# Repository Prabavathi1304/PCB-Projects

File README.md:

# PCB Design Projects

## Skills
- KiCad 10.0
- 2-Layer & 4-Layer PCB Design
- Schematic Design
- Gerber Export

## Projects
1. LED Circuit PCB
2. Power Supply PCB (L7805)
3. Arduino Shield PCB
4. MCU Board - ATtiny85 (4-Layer)

## Tools
- KiCad 10.0
- ERC & DRC Verification

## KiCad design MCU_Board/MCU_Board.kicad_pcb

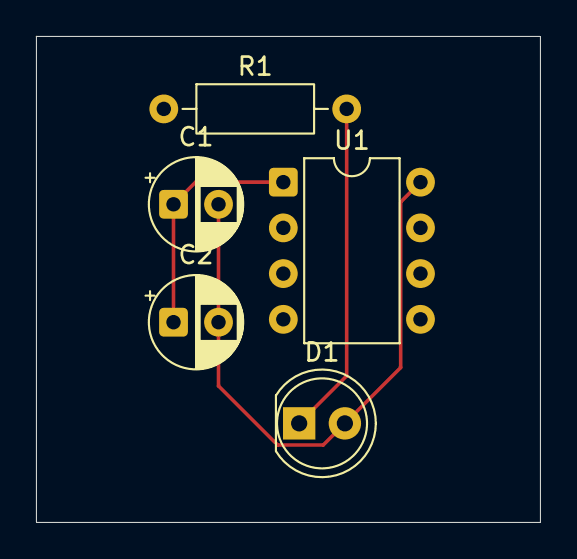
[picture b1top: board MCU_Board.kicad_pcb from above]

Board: 4 copper layers, 28.0 x 27.0 mm, 5 parts (0 on the bottom side), 3 nets.

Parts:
C1, C2: C; CP_Radial_D5.0mm_P2.50mm
D1: LED; LED_D5.0mm
R1: R; R_Axial_DIN0207_L6.3mm_D2.5mm_P10.16mm_Horizontal
U1: ATtiny85-20M; DIP-8_W7.62mm

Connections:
GND: C1.2, C2.2, D1.2 (A), U1.8 (GND)
unnamed: D1.1 (K), R1.2
VCC: C1.1, C2.1, U1.1 (~RESET/PB5)

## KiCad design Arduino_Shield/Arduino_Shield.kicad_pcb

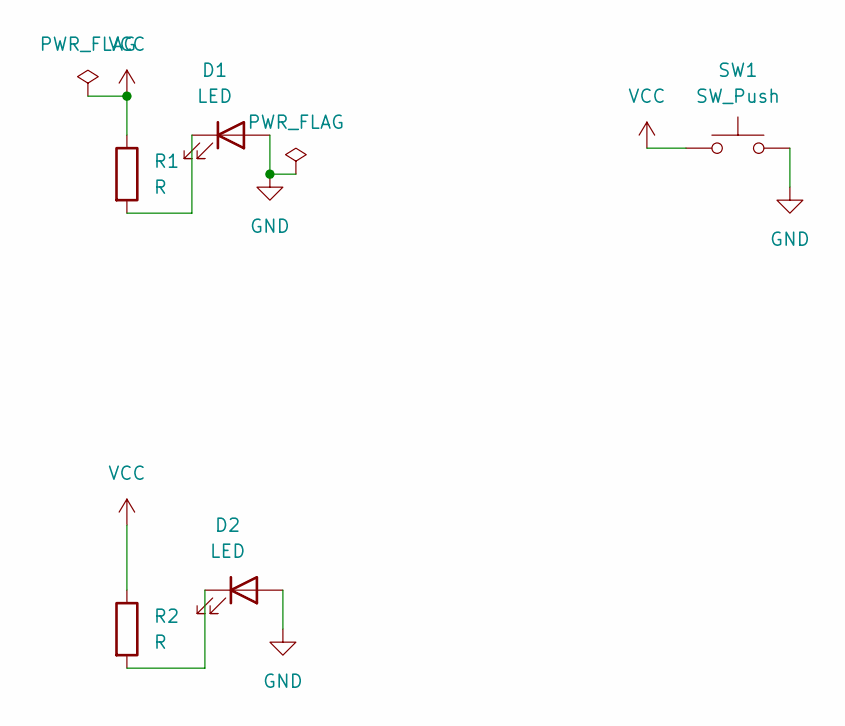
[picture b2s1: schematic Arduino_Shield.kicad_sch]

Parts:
D1, D2: LED; LED_D5.0mm
R1, R2: R; R_Axial_DIN0207_L6.3mm_D2.5mm_P10.16mm_Horizontal
SW1: SW_Push; SW_Push_1P1T-MP_NO_Horizontal_Alps_SKRTLAE010

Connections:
GND: D1.2 (A), D2.2 (A), SW1.2
unnamed: D1.1 (K), R1.2
unnamed: D2.1 (K), R2.2
VCC: R1.1, R2.1, SW1.1

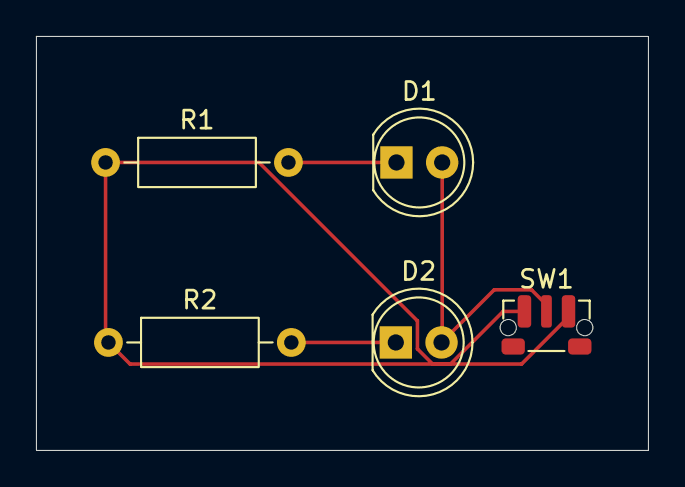
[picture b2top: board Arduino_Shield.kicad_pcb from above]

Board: 2 copper layers, 34.0 x 23.0 mm, 5 parts (0 on the bottom side), 4 nets.

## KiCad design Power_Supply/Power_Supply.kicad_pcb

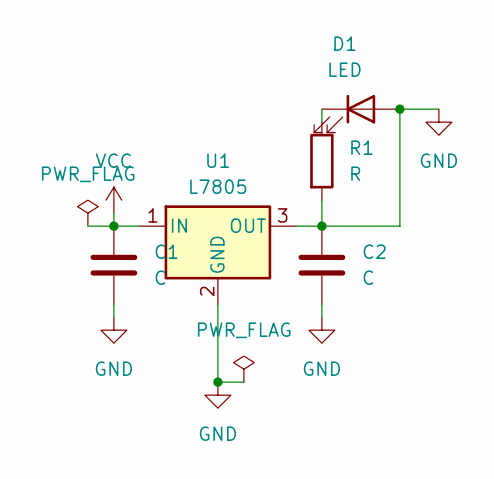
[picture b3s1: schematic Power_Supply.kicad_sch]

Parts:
C1, C2: C; CP_Radial_D5.0mm_P2.00mm
D1: LED; LED_D5.0mm
R1: R; R_Axial_DIN0207_L6.3mm_D2.5mm_P10.16mm_Horizontal
U1: L7805; TO-220-3_Horizontal_TabDown

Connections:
GND: C1.2, C2.1, C2.2, D1.2 (A), R1.2, U1.2 (GND), U1.3 (OUT)
unnamed: D1.1 (K), R1.1
VCC: C1.1, U1.1 (IN)

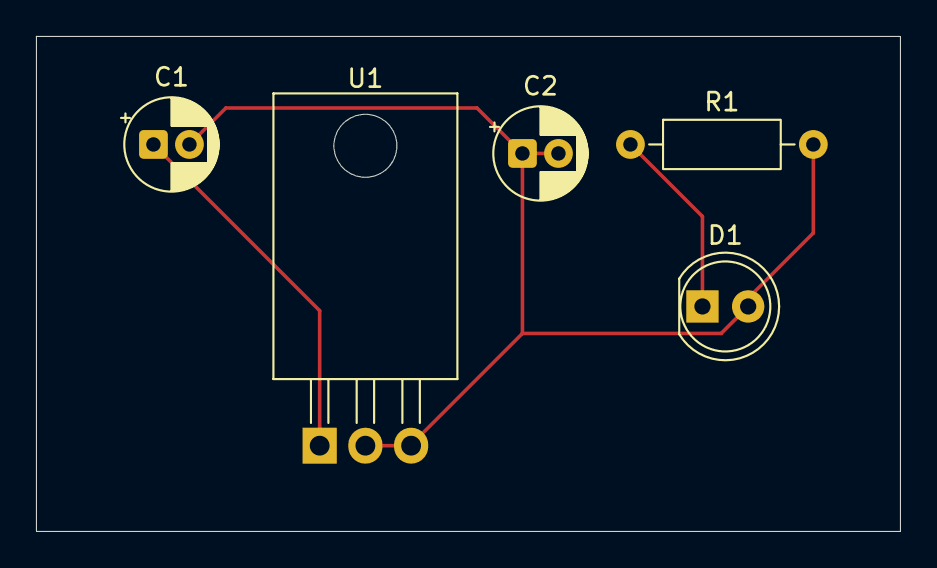
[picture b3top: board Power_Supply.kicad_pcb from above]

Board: 2 copper layers, 48.0 x 27.5 mm, 5 parts (0 on the bottom side), 3 nets.
